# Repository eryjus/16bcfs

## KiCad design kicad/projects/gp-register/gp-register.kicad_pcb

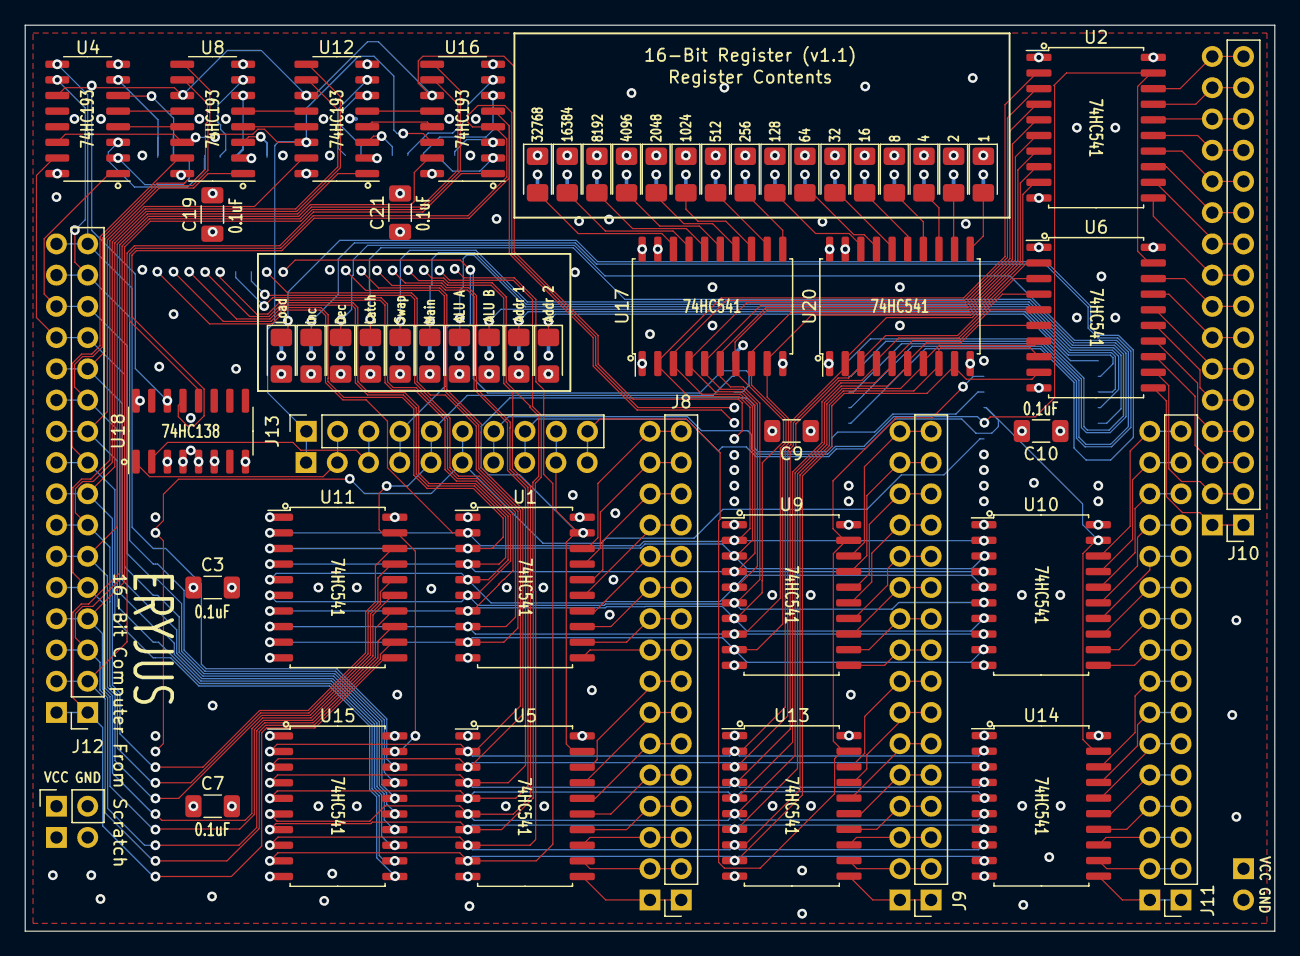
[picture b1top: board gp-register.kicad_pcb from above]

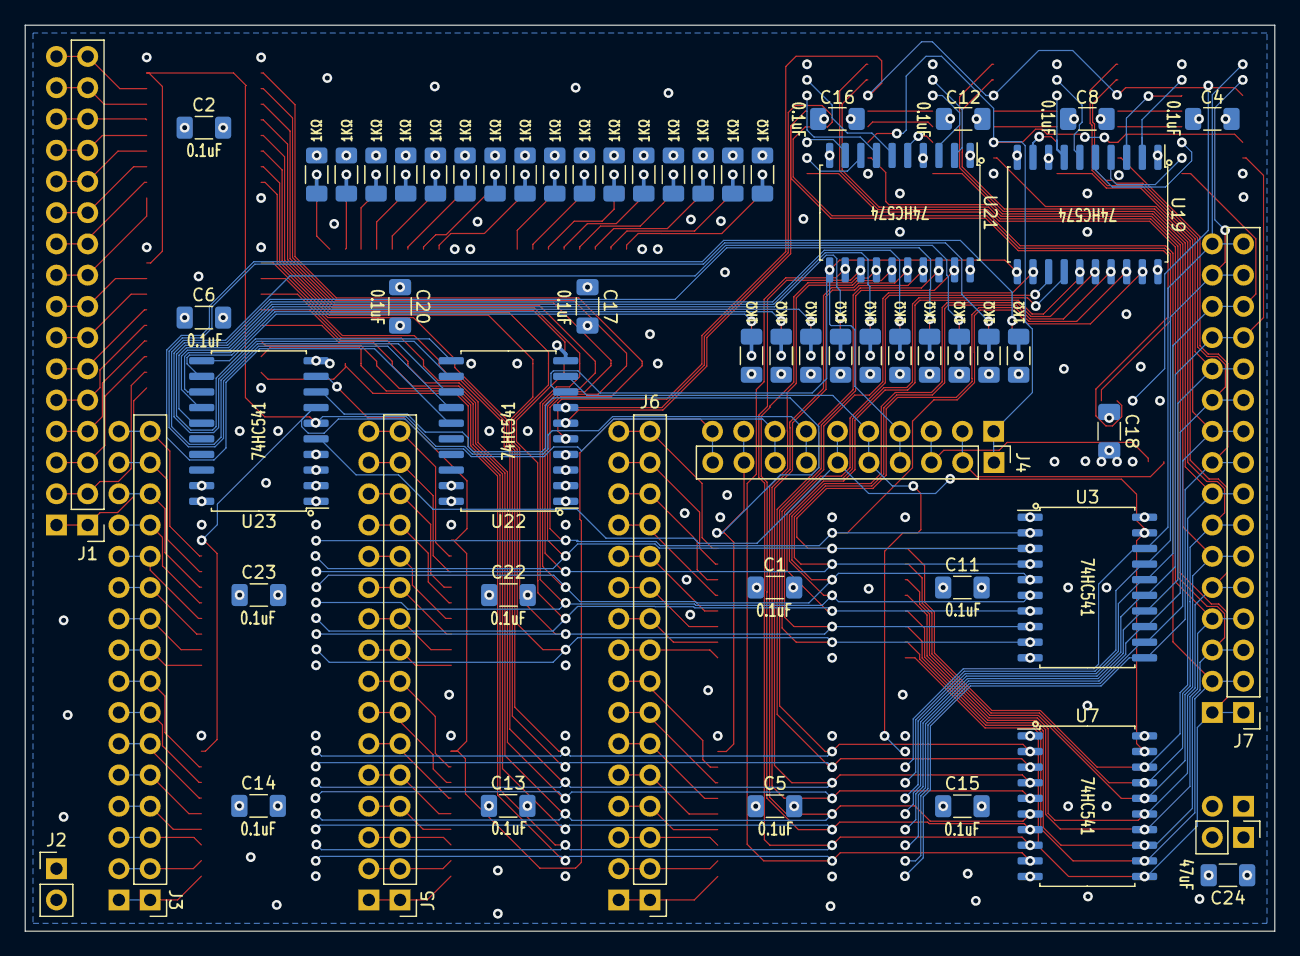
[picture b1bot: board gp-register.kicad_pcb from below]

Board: 4 copper layers, 101.6 x 73.7 mm, 114 parts (58 on the bottom side), 185 nets.

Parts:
C1, C2, C3, C4, C5, C6, C7, C8, C9, C10, C11, C12, C13, C14, C15, C16, C17, C18, C19, C20, C21, C22, C23: 0.1uF; C_1206_3216Metric_Pad1.33x1.80mm_HandSolder
C24: 47uF; C_1206_3216Metric_Pad1.33x1.80mm_HandSolder
D1, D2, D3, D4, D5, D6, D7, D8, D9, D10, D11, D12, D13, D14, D15, D16: Green; LED_1206_3216Metric_Pad1.42x1.75mm_HandSolder
D17, D18, D19, D20, D21, D22, D23, D24, D25, D26: Red; LED_1206_3216Metric_Pad1.42x1.75mm_HandSolder
J1: ALU Bus A; PinHeader_1x16_P2.54mm_Vertical
J2, J15: Power; PinHeader_1x02_P2.54mm_Vertical
J3: ALU Bus B; PinHeader_1x16_P2.54mm_Vertical
J4: Control Signals; PinHeader_1x10_P2.54mm_Vertical
J5: Address Bus 2; PinHeader_1x16_P2.54mm_Vertical
J6: Address Bus 1; PinHeader_1x16_P2.54mm_Vertical
J7: Main Bus; PinHeader_1x16_P2.54mm_Vertical
J8: Address Bus 1; PinSocket_1x16_P2.54mm_Vertical
J9: Address Bus 2; PinSocket_1x16_P2.54mm_Vertical
J10: ALU Bus A; PinSocket_1x16_P2.54mm_Vertical
J11: ALU Bus B; PinSocket_1x16_P2.54mm_Vertical
J12: Main Bus; PinSocket_1x16_P2.54mm_Vertical
J13: Control Signals; PinSocket_1x10_P2.54mm_Vertical
J14: Power; PinSocket_1x02_P2.54mm_Vertical
R1, R2, R3, R4, R5, R6, R7, R8, R9, R10, R11, R12, R13, R14, R15, R16: 220; R_1206_3216Metric_Pad1.30x1.75mm_HandSolder
R17, R18, R19, R20, R21, R22, R23, R24, R25, R26: 1K; R_1206_3216Metric_Pad1.30x1.75mm_HandSolder
U1, U2, U3, U5, U6, U7, U9, U10, U11, U13, U14, U15, U17, U20, U22, U23: 74HC541; SOIC-20W_7.5x12.8mm_P1.27mm
U4, U8, U12, U16: 74HC193; SOIC-16_3.9x9.9mm_P1.27mm
U18: 74HC138; SOIC-16_3.9x9.9mm_P1.27mm
U19, U21: 74HC574; SOIC-20W_7.5x12.8mm_P1.27mm

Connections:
/ALU A LED: D23.1 (K), U23.14 (Y4)
/ALU B LED: D24.1 (K), U23.13 (Y5)
/Add1 LED: D25.1 (K), U23.12 (Y6)
/Add2 LED: D26.1 (K), U23.11 (Y7)
/Bit 0 LED: D16.2 (A), U20.11 (Y7)
/Bit 1 LED: D15.2 (A), U20.12 (Y6)
/Bit 2 LED: D14.2 (A), U20.13 (Y5)
/Bit 3 LED: D13.2 (A), U20.14 (Y4)
/Bit 4 LED: D12.2 (A), U20.15 (Y3)
/Bit 5 LED: D11.2 (A), U20.16 (Y2)
/Bit 6 LED: D10.2 (A), U20.17 (Y1)
/Bit 7 LED: D9.2 (A), U20.18 (Y0)
/Bit 8 LED: D8.2 (A), U17.11 (Y7)
/Bit 9 LED: D7.2 (A), U17.12 (Y6)
/Bit A LED: D6.2 (A), U17.13 (Y5)
/Bit B LED: D5.2 (A), U17.14 (Y4)
/Bit C LED: D4.2 (A), U17.15 (Y3)
/Bit D LED: D3.2 (A), U17.16 (Y2)
/Bit E LED: D2.2 (A), U17.17 (Y1)
/Bit F LED: D1.2 (A), U17.18 (Y0)
/Dec LED: D19.1 (K), U22.13 (Y5)
/Inc LED: D18.1 (K), U22.14 (Y4)
/Latch LED: D20.1 (K), U22.12 (Y6)
/Load LED: D17.1 (K), U22.15 (Y3)
/Main LED: D22.1 (K), U23.15 (Y3)
/Swap LED: D21.1 (K), U22.11 (Y7)
ALUAAssert: J4.7, J13.7, U2.19 (G2), U6.19 (G2), U23.6 (A4)
ALUABit0: J1.1, J10.1, U6.11 (Y7)
ALUABit1: J1.2, J10.2, U6.12 (Y6)
ALUABit2: J1.3, J10.3, U6.13 (Y5)
ALUABit3: J1.4, J10.4, U6.14 (Y4)
ALUABit4: J1.5, J10.5, U6.15 (Y3)
ALUABit5: J1.6, J10.6, U6.16 (Y2)
ALUABit6: J1.7, J10.7, U6.17 (Y1)
ALUABit7: J1.8, J10.8, U6.18 (Y0)
ALUABit8: J1.9, J10.9, U2.11 (Y7)
ALUABit9: J1.10, J10.10, U2.12 (Y6)
ALUABitA: J1.11, J10.11, U2.13 (Y5)
ALUABitB: J1.12, J10.12, U2.14 (Y4)
ALUABitC: J1.13, J10.13, U2.15 (Y3)
ALUABitD: J1.14, J10.14, U2.16 (Y2)
ALUABitE: J1.15, J10.15, U2.17 (Y1)
ALUABitF: J1.16, J10.16, U2.18 (Y0)
ALUBAssert: J4.8, J13.8, U10.19 (G2), U14.19 (G2), U23.7 (A5)
ALUBBit0: J3.1, J11.1, U14.11 (Y7)
ALUBBit1: J3.2, J11.2, U14.12 (Y6)
ALUBBit2: J3.3, J11.3, U14.13 (Y5)
ALUBBit3: J3.4, J11.4, U14.14 (Y4)
ALUBBit4: J3.5, J11.5, U14.15 (Y3)
ALUBBit5: J3.6, J11.6, U14.16 (Y2)
ALUBBit6: J3.7, J11.7, U14.17 (Y1)
ALUBBit7: J3.8, J11.8, U14.18 (Y0)
ALUBBit8: J3.9, J11.9, U10.11 (Y7)
ALUBBit9: J3.10, J11.10, U10.12 (Y6)
ALUBBitA: J3.11, J11.11, U10.13 (Y5)
ALUBBitB: J3.12, J11.12, U10.14 (Y4)
ALUBBitC: J3.13, J11.13, U10.15 (Y3)
ALUBBitD: J3.14, J11.14, U10.16 (Y2)
ALUBBitE: J3.15, J11.15, U10.17 (Y1)
ALUBBitF: J3.16, J11.16, U10.18 (Y0)
AddrBus1Assert: J4.9, J13.9, U1.19 (G2), U5.19 (G2), U23.8 (A6)
AddrBus1Bit0: J6.1, J8.1, U5.11 (Y7)
AddrBus1Bit1: J6.2, J8.2, U5.12 (Y6)
AddrBus1Bit2: J6.3, J8.3, U5.13 (Y5)
AddrBus1Bit3: J6.4, J8.4, U5.14 (Y4)
AddrBus1Bit4: J6.5, J8.5, U5.15 (Y3)
AddrBus1Bit5: J6.6, J8.6, U5.16 (Y2)
AddrBus1Bit6: J6.7, J8.7, U5.17 (Y1)
AddrBus1Bit7: J6.8, J8.8, U5.18 (Y0)
AddrBus1Bit8: J6.9, J8.9, U1.11 (Y7)
AddrBus1Bit9: J6.10, J8.10, U1.12 (Y6)
AddrBus1BitA: J6.11, J8.11, U1.13 (Y5)
AddrBus1BitB: J6.12, J8.12, U1.14 (Y4)
AddrBus1BitC: J6.13, J8.13, U1.15 (Y3)
AddrBus1BitD: J6.14, J8.14, U1.16 (Y2)
AddrBus1BitE: J6.15, J8.15, U1.17 (Y1)
AddrBus1BitF: J6.16, J8.16, U1.18 (Y0)
AddrBus2Assert: J4.10, J13.10, U9.19 (G2), U13.19 (G2), U23.9 (A7)
AddrBus2Bit0: J5.1, J9.1, U13.11 (Y7)
AddrBus2Bit1: J5.2, J9.2, U13.12 (Y6)
AddrBus2Bit2: J5.3, J9.3, U13.13 (Y5)
AddrBus2Bit3: J5.4, J9.4, U13.14 (Y4)
AddrBus2Bit4: J5.5, J9.5, U13.15 (Y3)
AddrBus2Bit5: J5.6, J9.6, U13.16 (Y2)
AddrBus2Bit6: J5.7, J9.7, U13.17 (Y1)
AddrBus2Bit7: J5.8, J9.8, U13.18 (Y0)
AddrBus2Bit8: J5.9, J9.9, U9.11 (Y7)
AddrBus2Bit9: J5.10, J9.10, U9.12 (Y6)
AddrBus2BitA: J5.11, J9.11, U9.13 (Y5)
AddrBus2BitB: J5.12, J9.12, U9.14 (Y4)
AddrBus2BitC: J5.13, J9.13, U9.15 (Y3)
AddrBus2BitD: J5.14, J9.14, U9.16 (Y2)
AddrBus2BitE: J5.15, J9.15, U9.17 (Y1)
AddrBus2BitF: J5.16, J9.16, U9.18 (Y0)
AndLatch: J4.4, J13.4, U19.11 (Cp), U21.11 (Cp), U22.8 (A6)
Clear: J4.1, J13.1, U4.14 (CLR), U8.14 (CLR), U12.14 (CLR), U16.14 (CLR)
CounterBit0: U16.3 (QA), U21.9 (D7)
CounterBit1: U16.2 (QB), U21.8 (D6)
CounterBit2: U16.6 (QC), U21.7 (D5)
CounterBit3: U16.7 (QD), U21.6 (D4)
CounterBit4: U12.3 (QA), U21.5 (D3)
CounterBit5: U12.2 (QB), U21.4 (D2)
CounterBit6: U12.6 (QC), U21.3 (D1)
CounterBit7: U12.7 (QD), U21.2 (D0)
CounterBit8: U8.3 (QA), U19.9 (D7)
CounterBit9: U8.2 (QB), U19.8 (D6)
CounterBitA: U8.6 (QC), U19.7 (D5)
CounterBitB: U8.7 (QD), U19.6 (D4)
CounterBitC: U4.3 (QA), U19.5 (D3)
CounterBitD: U4.2 (QB), U19.4 (D2)
CounterBitE: U4.6 (QC), U19.3 (D1)
CounterBitF: U4.7 (QD), U19.2 (D0)
Dec: U16.4 (DOWN), U18.12 (O3), U22.7 (A5)
GNDREF: C1.2, C2.2, C3.2, C4.2, C5.2, C6.2, C7.2, C8.2, C9.2, C10.2, C11.2, C12.2, C13.2, C14.2, C15.2, C16.2, C17.2, C18.2, C19.2, C20.2, C21.2, C22.2, C23.2, C24.2, J2.2, J14.2, J15.2, R1.1, R2.1, R3.1, R4.1, R5.1, R6.1, R7.1, R8.1, R9.1, R10.1, R11.1, R12.1, R13.1, R14.1, R15.1, R16.1, U1.1 (G1), U1.10 (GND), U2.1 (G1), U2.10 (GND), U3.1 (G1), U3.10 (GND), U4.8 (GND), U5.1 (G1), U5.10 (GND), U6.1 (G1), U6.10 (GND), U7.1 (G1), U7.10 (GND), U8.8 (GND), U9.1 (G1), U9.10 (GND), U10.1 (G1), U10.10 (GND), U11.1 (G1), U11.10 (GND), U12.8 (GND), U13.1 (G1), U13.10 (GND), U14.1 (G1), U14.10 (GND), U15.1 (G1), U15.10 (GND), U16.8 (GND), U17.1 (G1), U17.10 (GND), U17.19 (G2), U18.3 (A2), U18.4 (E1), U18.5 (E2), U18.8 (GND), U19.1 (OE), U19.10 (GND), U20.1 (G1), U20.10 (GND), U20.19 (G2), U21.1 (OE), U21.10 (GND), U22.1 (G1), U22.2 (A0), U22.3 (A1), U22.4 (A2), U22.10 (GND), U22.19 (G2), U23.1 (G1), U23.2 (A0), U23.3 (A1), U23.4 (A2), U23.10 (GND), U23.19 (G2)
Inc: U16.5 (UP), U18.13 (O2), U22.6 (A4)
Load: U4.11 (~LOAD), U8.11 (~LOAD), U12.11 (~LOAD), U16.11 (~LOAD), U18.14 (O1), U22.5 (A3)
MainBit0: J7.1, J12.1, U7.11 (Y7), U11.11 (Y7), U16.15 (A)
MainBit1: J7.2, J12.2, U7.12 (Y6), U11.12 (Y6), U16.1 (B)
MainBit2: J7.3, J12.3, U7.13 (Y5), U11.13 (Y5), U16.10 (C)
MainBit3: J7.4, J12.4, U7.14 (Y4), U11.14 (Y4), U16.9 (D)
MainBit4: J7.5, J12.5, U7.15 (Y3), U11.15 (Y3), U12.15 (A)
MainBit5: J7.6, J12.6, U7.16 (Y2), U11.16 (Y2), U12.1 (B)
MainBit6: J7.7, J12.7, U7.17 (Y1), U11.17 (Y1), U12.10 (C)
MainBit7: J7.8, J12.8, U7.18 (Y0), U11.18 (Y0), U12.9 (D)
MainBit8: J7.9, J12.9, U3.11 (Y7), U8.15 (A), U15.11 (Y7)
MainBit9: J7.10, J12.10, U3.12 (Y6), U8.1 (B), U15.12 (Y6)
MainBitA: J7.11, J12.11, U3.13 (Y5), U8.10 (C), U15.13 (Y5)
MainBitB: J7.12, J12.12, U3.14 (Y4), U8.9 (D), U15.14 (Y4)
MainBitC: J7.13, J12.13, U3.15 (Y3), U4.15 (A), U15.15 (Y3)
MainBitD: J7.14, J12.14, U3.16 (Y2), U4.1 (B), U15.16 (Y2)
MainBitE: J7.15, J12.15, U3.17 (Y1), U4.10 (C), U15.17 (Y1)
MainBitF: J7.16, J12.16, U3.18 (Y0), U4.9 (D), U15.18 (Y0)
MainBusAssert: J4.6, J13.6, U3.19 (G2), U7.19 (G2), U23.5 (A3)
unnamed: D1.1 (K), R1.2
unnamed: D2.1 (K), R2.2
unnamed: D3.1 (K), R3.2
unnamed: D4.1 (K), R4.2
unnamed: D5.1 (K), R5.2
unnamed: D6.1 (K), R6.2
unnamed: D7.1 (K), R7.2
unnamed: D8.1 (K), R8.2
unnamed: D9.1 (K), R9.2
unnamed: D10.1 (K), R10.2
unnamed: D11.1 (K), R11.2
unnamed: D12.1 (K), R12.2
unnamed: D13.1 (K), R13.2
unnamed: D14.1 (K), R14.2
unnamed: D15.1 (K), R15.2
unnamed: D16.1 (K), R16.2
unnamed: D17.2 (A), R17.2
unnamed: D18.2 (A), R18.2
unnamed: D19.2 (A), R19.2
unnamed: D20.2 (A), R20.2
unnamed: D21.2 (A), R21.2
unnamed: D22.2 (A), R22.2
unnamed: D23.2 (A), R23.2
unnamed: D24.2 (A), R24.2
unnamed: D25.2 (A), R25.2
unnamed: D26.2 (A), R26.2
unnamed: U4.4 (DOWN), U8.13 (~BO)
unnamed: U4.5 (UP), U8.12 (~CO)
unnamed: U12.4 (DOWN), U16.13 (~BO)
unnamed: U12.5 (UP), U16.12 (~CO)
unnamed: U8.4 (DOWN), U12.13 (~BO)
unnamed: U8.5 (UP), U12.12 (~CO)
RegBit0: U5.9 (A7), U6.9 (A7), U7.9 (A7), U13.9 (A7), U14.9 (A7), U15.9 (A7), U20.9 (A7), U21.12 (Q7)
RegBit1: U5.8 (A6), U6.8 (A6), U7.8 (A6), U13.8 (A6), U14.8 (A6), U15.8 (A6), U20.8 (A6), U21.13 (Q6)
RegBit2: U5.7 (A5), U6.7 (A5), U7.7 (A5), U13.7 (A5), U14.7 (A5), U15.7 (A5), U20.7 (A5), U21.14 (Q5)
RegBit3: U5.6 (A4), U6.6 (A4), U7.6 (A4), U13.6 (A4), U14.6 (A4), U15.6 (A4), U20.6 (A4), U21.15 (Q4)
RegBit4: U5.5 (A3), U6.5 (A3), U7.5 (A3), U13.5 (A3), U14.5 (A3), U15.5 (A3), U20.5 (A3), U21.16 (Q3)
RegBit5: U5.4 (A2), U6.4 (A2), U7.4 (A2), U13.4 (A2), U14.4 (A2), U15.4 (A2), U20.4 (A2), U21.17 (Q2)
RegBit6: U5.3 (A1), U6.3 (A1), U7.3 (A1), U13.3 (A1), U14.3 (A1), U15.3 (A1), U20.3 (A1), U21.18 (Q1)
RegBit7: U5.2 (A0), U6.2 (A0), U7.2 (A0), U13.2 (A0), U14.2 (A0), U15.2 (A0), U20.2 (A0), U21.19 (Q0)
RegBit8: U1.9 (A7), U2.9 (A7), U3.9 (A7), U9.9 (A7), U10.9 (A7), U11.9 (A7), U17.9 (A7), U19.12 (Q7)
RegBit9: U1.8 (A6), U2.8 (A6), U3.8 (A6), U9.8 (A6), U10.8 (A6), U11.8 (A6), U17.8 (A6), U19.13 (Q6)
RegBitA: U1.7 (A5), U2.7 (A5), U3.7 (A5), U9.7 (A5), U10.7 (A5), U11.7 (A5), U17.7 (A5), U19.14 (Q5)
RegBitB: U1.6 (A4), U2.6 (A4), U3.6 (A4), U9.6 (A4), U10.6 (A4), U11.6 (A4), U17.6 (A4), U19.15 (Q4)
RegBitC: U1.5 (A3), U2.5 (A3), U3.5 (A3), U9.5 (A3), U10.5 (A3), U11.5 (A3), U17.5 (A3), U19.16 (Q3)
RegBitD: U1.4 (A2), U2.4 (A2), U3.4 (A2), U9.4 (A2), U10.4 (A2), U11.4 (A2), U17.4 (A2), U19.17 (Q2)
RegBitE: U1.3 (A1), U2.3 (A1), U3.3 (A1), U9.3 (A1), U10.3 (A1), U11.3 (A1), U17.3 (A1), U19.18 (Q1)
RegBitF: U1.2 (A0), U2.2 (A0), U3.2 (A0), U9.2 (A0), U10.2 (A0), U11.2 (A0), U17.2 (A0), U19.19 (Q0)
RegisterInput0: J4.2, J13.2, U18.1 (A0)
RegisterInput1: J4.3, J13.3, U18.2 (A1)
SwapBusAssert: J4.5, J13.5, U11.19 (G2), U15.19 (G2), U22.9 (A7)
VCC: C1.1, C2.1, C3.1, C4.1, C5.1, C6.1, C7.1, C8.1, C9.1, C10.1, C11.1, C12.1, C13.1, C14.1, C15.1, C16.1, C17.1, C18.1, C19.1, C20.1, C21.1, C22.1, C23.1, C24.1, J2.1, J14.1, J15.1, R17.1, R18.1, R19.1, R20.1, R21.1, R22.1, R23.1, R24.1, R25.1, R26.1, U1.20 (VCC), U2.20 (VCC), U3.20 (VCC), U4.16 (VCC), U5.20 (VCC), U6.20 (VCC), U7.20 (VCC), U8.16 (VCC), U9.20 (VCC), U10.20 (VCC), U11.20 (VCC), U12.16 (VCC), U13.20 (VCC), U14.20 (VCC), U15.20 (VCC), U16.16 (VCC), U17.20 (VCC), U18.6 (E3), U18.16 (VCC), U19.20 (VCC), U20.20 (VCC), U21.20 (VCC), U22.20 (VCC), U23.20 (VCC)

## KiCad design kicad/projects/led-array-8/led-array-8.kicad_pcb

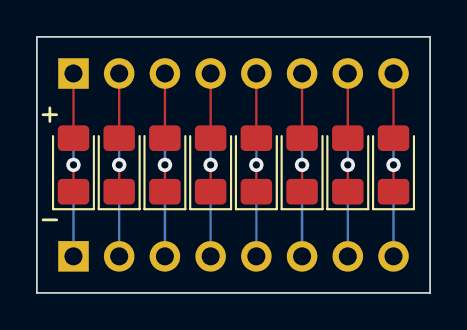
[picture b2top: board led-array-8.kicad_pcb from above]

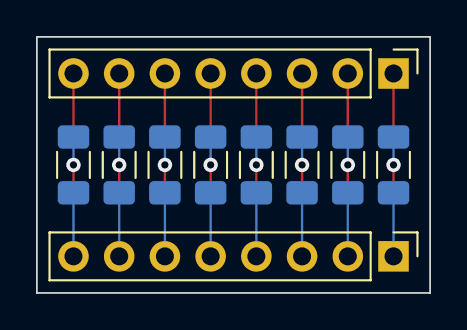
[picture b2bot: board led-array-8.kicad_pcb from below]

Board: 2 copper layers, 21.8 x 14.2 mm, 18 parts (10 on the bottom side), 24 nets.

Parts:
D1, D2, D3, D4, D5, D6, D7, D8: LED; LED_1206_3216Metric_Pad1.42x1.75mm_HandSolder
J1, J2: Conn_01x16_Pin; PinHeader_1x08_P2.54mm_Vertical
R1, R2, R3, R4, R5, R6, R7, R8: R; R_1206_3216Metric_Pad1.30x1.75mm_HandSolder

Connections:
unnamed: D1.2 (A), J1.1
unnamed: D1.1 (K), R1.1
unnamed: D2.2 (A), J1.2
unnamed: D2.1 (K), R2.1
unnamed: D3.2 (A), J1.3
unnamed: D3.1 (K), R3.1
unnamed: D4.2 (A), J1.4
unnamed: D4.1 (K), R4.1
unnamed: D5.2 (A), J1.5
unnamed: D5.1 (K), R5.1
unnamed: D6.2 (A), J1.6
unnamed: D6.1 (K), R6.1
unnamed: D7.2 (A), J1.7
unnamed: D7.1 (K), R7.1
unnamed: D8.2 (A), J1.8
unnamed: D8.1 (K), R8.1
unnamed: J2.1, R1.2
unnamed: J2.2, R2.2
unnamed: J2.3, R3.2
unnamed: J2.4, R4.2
unnamed: J2.5, R5.2
unnamed: J2.6, R6.2
unnamed: J2.7, R7.2
unnamed: J2.8, R8.2
